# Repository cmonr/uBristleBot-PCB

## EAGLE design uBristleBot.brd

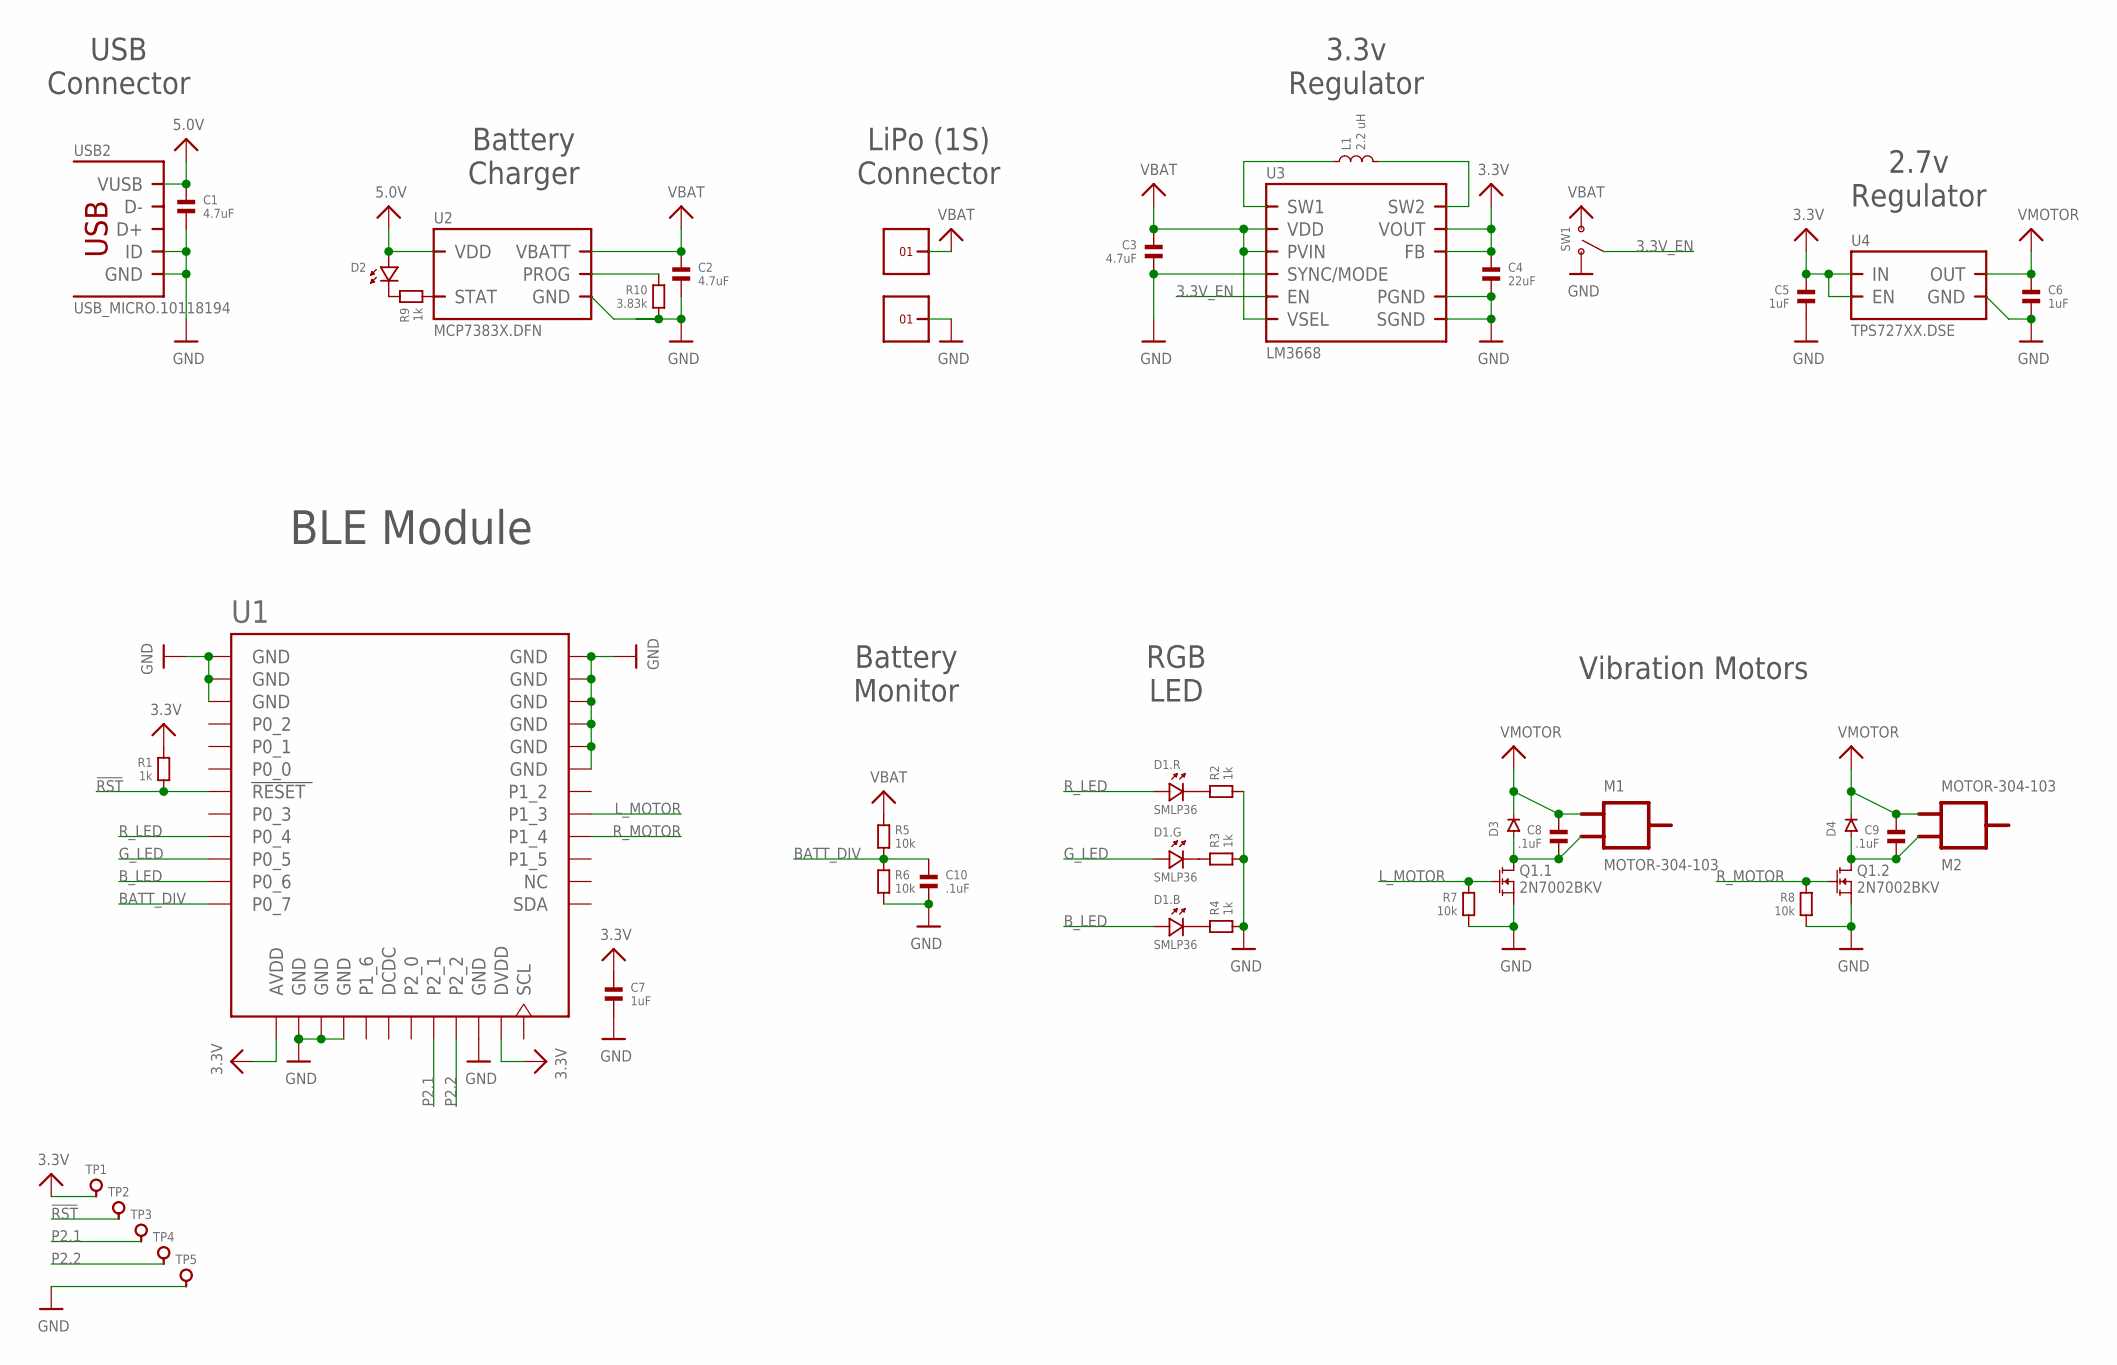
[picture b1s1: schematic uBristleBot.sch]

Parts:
C1, C2, C3: 4.7uF; 0603
C4: 22uF; 0603
C5, C6, C7: 1uF; 0402
C8, C9, C10: .1uF; 0402
D1: SMLP36; 0604
D2: LED.0402; 0402.LED
D3, D4: DIODE.SOD-523F; SOD-523F
L1: 2.2 uH; SDR0403
M1, M2: MOTOR-304-103; 304-103
Q1: 2N7002BKV; SOT666
R1, R2, R3, R4, R9: 1k; 0402
R5, R6, R7, R8: 10k; 0402
R10: 3.83k; 0402
SW1: SSAJ110100
TP1, TP2, TP3, TP4, TP5: PCB_PAD.42MIL; 0906-0_PAD
U1: BLE121LR-VISUAL-A; BLE121LR-A
U2: MCP7383X.DFN; DFN8-3X2.PAD
U3: LM3668; LLP.12.3X3MM
U4: TPS727XX.DSE; DSE
U$31, U$34: 1X1
USB2: USB_MICRO.10118194; 10118194

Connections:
3.3V: C4.1, C5.1, C7.1, R1.1, TP1.PAD, U1.AVDD, U1.DVDD, U3.1 (VOUT), U3.12 (FB), U4.4 (EN), U4.6 (IN)
3.3V_EN: SW1.C (COM), U3.6 (EN)
5.0V: C1.1, D2.P$1 (1), U2.1 (VDD), U2.2 (VDD), USB2.1 (VUSB)
!RST: R1.2, TP2.PAD, U1.RESET
BATT_DIV: C10.1, R5.2, R6.1, U1.P0_7
B_LED: D1.1 (+), U1.P0_6
GND: C1.2, C2.2, C3.2, C4.2, C5.2, C6.2, C7.2, C10.2, Q1.1 (S), Q1.4 (S), R2.2, R3.2, R4.2, R6.2, R7.2, R8.2, R10.2, SW1.1 (A), TP5.PAD, U1.GND, U1.GND@2 (GND), U1.GND@3 (GND), U1.GND@4 (GND), U1.GND@5 (GND), U1.GND@6 (GND), U1.GND@7 (GND), U1.GND@8 (GND), U1.GND@9 (GND), U1.GND@10 (GND), U1.GND@11 (GND), U1.GND@12 (GND), U1.GND@13 (GND), U2.6 (GND), U2.PAD (GND), U3.3 (PGND), U3.8 (SGND), U3.9 (SGND), U3.10 (SYNC/MODE), U3.PAD (SGND), U4.3 (GND), U$34.1, USB2.4 (ID), USB2.5 (GND), USB2.PAD@1 (GND), USB2.PAD@2 (GND), USB2.PAD@3 (GND), USB2.PAD@4 (GND), USB2.PAD@5 (GND), USB2.PAD@6 (GND), USB2.PAD@7 (GND), USB2.PAD@8 (GND), USB2.PAD@9 (GND), USB2.PAD@10 (GND), USB2.PAD@11 (GND), USB2.PAD@12 (GND), USB2.PAD@13 (GND), USB2.PAD@14 (GND), USB2.PAD@15 (GND), USB2.PAD@16 (GND)
G_LED: D1.3 (+), U1.P0_5
L_MOTOR: Q1.2 (G), R7.1, U1.P1_3
unnamed: D1.5 (-), R2.1
unnamed: D1.4 (-), R3.1
unnamed: D1.6 (-), R4.1
unnamed: L1.1, U3.4 (SW1)
unnamed: C8.2, D3.A, M1.2, Q1.6 (D)
unnamed: C9.2, D4.A, M2.1, Q1.3 (D)
unnamed: R9.2, U2.5 (STAT)
unnamed: D2.P$2 (2), R9.1
unnamed: R10.1, U2.8 (PROG)
unnamed: L1.2, U3.2 (SW2)
P2.1: TP3.PAD, U1.P2_1
P2.2: TP4.PAD, U1.P2_2
R_LED: D1.2 (+), U1.P0_4
R_MOTOR: Q1.5 (G), R8.1, U1.P1_4
VBAT: C2.1, C3.1, R5.1, SW1.2 (B), U2.3 (VBATT), U2.4 (VBATT), U3.5 (PVIN), U3.7 (VDD), U3.11 (VSEL), U$31.1
VMOTOR: C6.1, C8.1, C9.1, D3.C, D4.C, M1.1, M2.2, U4.1 (OUT)

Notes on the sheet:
USB Connector
LiPo (1S) Connector
Battery Charger
3.3v Regulator
2.7v Regulator
BLE Module
Battery Monitor
RGB LED
Vibration Motors

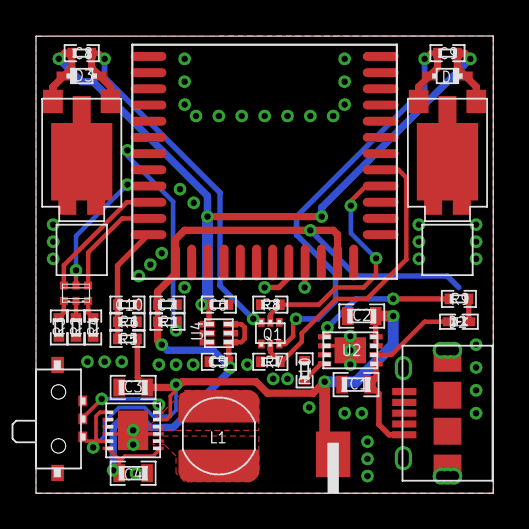
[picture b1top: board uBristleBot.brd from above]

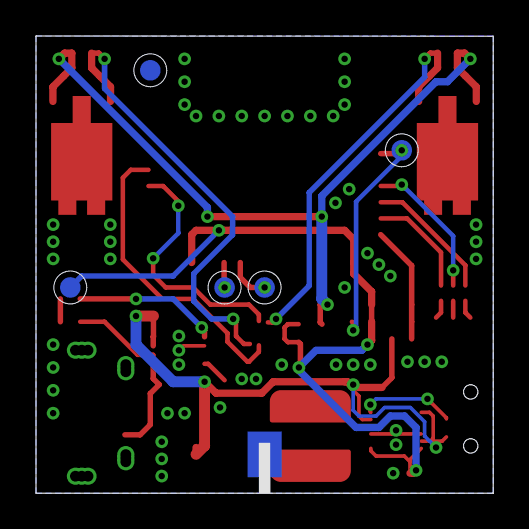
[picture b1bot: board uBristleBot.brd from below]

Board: 2 copper layers, 25.4 x 25.4 mm, 41 parts (6 on the bottom side), 25 nets.

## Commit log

2015-11-20 Initial Commit. Schematic ready for review
2015-11-20 Generated image previews
2015-11-21 Component placement mostly complete. Beginning layout
2015-11-21 Layout complete and ready for review
2016-01-17 Updated Inuctor and LED layer parts, and moved PWM pins. Ripped up programming connector in prep for Pogo Pins
2016-01-17 Updated prevew images
2016-01-18 Finished layout of v0.2
2016-01-18 Updated preview images
2016-01-18 Tweaked layout for GND plane
2016-01-18 Ading zip for quick ordering
2018-10-01 Added csv BoM. Not sure how that was missed...
2018-10-01 Corrected exported csv to _actually_ use commas. FFS Eagle...

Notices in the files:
parts and their libraries:
microbuilder: This work is placed in the public domain, and may be freely used for commercial and non-commercial work with the following conditions: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
